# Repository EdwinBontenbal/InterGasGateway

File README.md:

# InterGasGateway
Arduino (esp8266) Hardware/Software to monitor a Intergas boiler over rs232 interface (x5) of the intergas boiler to Domotica Software with the use of MQTT.

# What to expect
This project consists of:
-  Hardware -> Cable diagram of between the IntergasGateway and the boiler
-  Hardware -> IntergasGateway Schemetic based on KiKad
-  Hardware -> IntergasGateway PCB based on KiKad
-  Software -> IntergasGateway sketch to be placed on arduino eps8266

# Hardware
A few requirements, set by myself, according to the hardware:
- Should be able to run paricitair on the boiler x5 PCB connector (without external power)
- High input RX/TX impedance
- RX/TX gavanically separated
- PCB should fitted in housing
- All parts can be ordered at Aliexpress
- PCb Easy to be ordered 
- Easy to build

# Software
A few requirements, set by myself, according to the software:
- Code should easy to read and logically setup
- Code should be expandable with ic3 burner
- Code should be based on statemachines
- Good serial debugging possibilities
- Output of retrieved data should be pushed to the serial port
- Output of retrieved data should be pushed to a mqtt listner (domotica software independent)
- Scheduled retrievel of data should be possible
- Reading the serial port should be fail save

# Usefull information
- When using the serial monitor function please set the speed to 115200
- The Gl_ParameterList als has a parameter to debug the serial port (ras data)

# Used tools
- Visual Studio code + platrformIO
- KiCad
- MQTT Explorer
- Python decompiler
- yed

# General requirements
- Based on opensource
- Robust
- Well documented
- Low cost
- Components easy to find and easy to order
- Reproducable

# Good to know
- Intergas has it's own software (IDS) for monitoring the X5 port of the boiler. You can download the original software at this link (https://www.intergas-verwarming.nl/zakelijk/download-ids-software/). The only thing you have to do is registrer yourself. The software was extremly usefull during the development of the arduino software.

# Help needed
I own a intergas boiler of type ic2 so I was able to develop the arduino parse code for the ic2 telegrams. I want to add and test also the ic3 telegrams therefor I need someone to test for me the arduino code. 

# Link to get the board

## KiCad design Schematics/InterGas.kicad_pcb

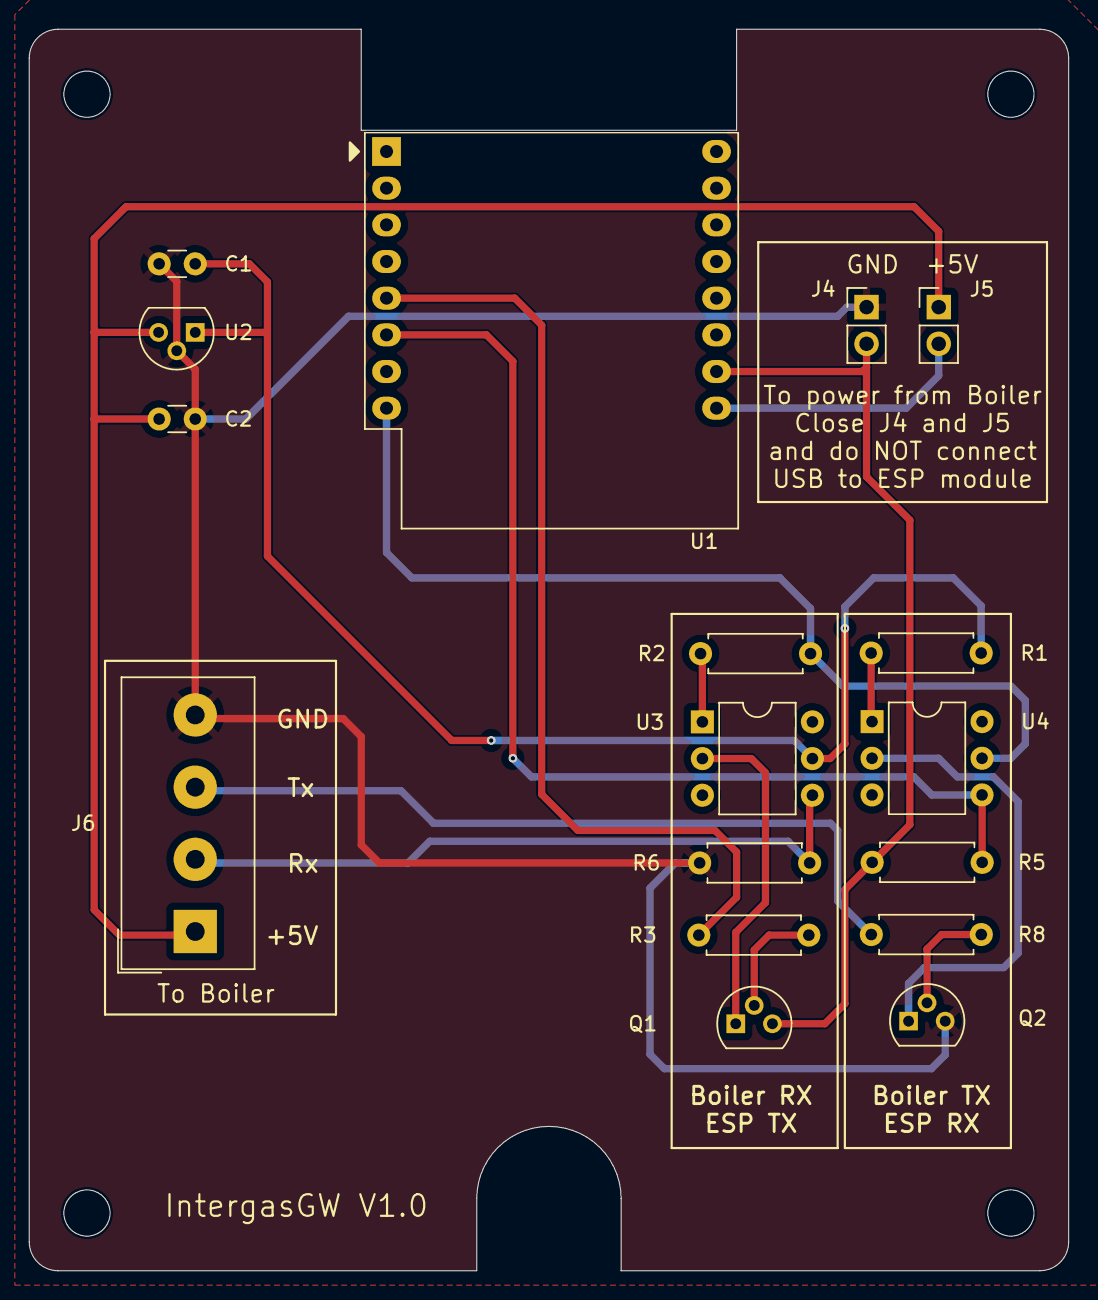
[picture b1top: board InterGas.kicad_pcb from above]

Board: 2 copper layers, 72.0 x 86.0 mm, 21 parts (0 on the bottom side), 16 nets.

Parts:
C1: 10nF; C_Disc_D3.0mm_W1.6mm_P2.50mm
C2: 100nF; C_Disc_D3.0mm_W1.6mm_P2.50mm
H1, H2, H3, H4: MountingHole; MountingHole_3.2mm_M3
J4, J5: Conn_01x02_Pin; PinHeader_1x02_P2.54mm_Vertical
J6: Screw_Terminal_01x04; Altech_AK100_1x04_P5.00mm
Q1, Q2: BC337; TO-92L
R1, R2, R3, R5, R6, R8: 1K; R_Axial_DIN0207_L6.3mm_D2.5mm_P7.62mm_Horizontal
U1: WEMOS_D1_mini; WEMOS_D1_mini_light
U2: L78L33_TO92; TO-92L
U3, U4: 4N25; DIP-6_W7.62mm

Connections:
+3V3 ESP8266: R2.2, U1.8 (3V3), U4.5
+3V3 Intergas: C1.1, R1.2, U2.1 (VO), U3.5
+5V ESP8266: J5.2, U1.9 (5V)
+5V Intergas: C2.1, J5.1, J6.1, U2.3 (VI)
Boiler_Rx: J6.2, R6.2, U3.4
Boiler_Tx: J6.3, R8.1
ESP32_Rx: R5.2, U1.6 (MOSI/D7), U4.4
ESP32_Tx: R3.1, U1.5 (MISO/D6)
GND ESP8266: J4.2, Q1.3 (E), R5.1, U1.10 (GND)
GND Intergas: C1.2, C2.2, J4.1, J6.4, Q2.3 (E), R6.1, U2.2 (GND)
unnamed: Q1.2 (B), R3.2
unnamed: Q1.1 (C), U3.2
unnamed: Q2.2 (B), R8.2
unnamed: Q2.1 (C), U4.2
unnamed: R1.1, U4.1
unnamed: R2.1, U3.1

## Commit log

2025-02-03 UpdatePictures
    1st picture update
2025-02-03 1st start schematics
2025-02-04 update
    update
2025-02-05 Update
    Update information found
2025-02-12 Create CasingDimensions.PNG
    Added dimensions of the casing for PCB
2025-02-12 Create DrillHoles_PCB.png
    Drill holes for PCB
2025-03-02 Test Setup
2025-04-06 OpenHab Files
    Openhab files for importing channel config
2025-04-06 Update README.md
    First step for documenting the project
2025-04-15 Update IntergasGateway__V0_9.ino
    Added reconnect function
    Added millis() rolover function
    Added duration of telegram
2025-04-16 Update README.md
    Added Hardware/Software requirements
2025-07-06 Lots of updates including statemachine
2025-08-15 Update Schematics
2025-08-15 Update with last code
    Update with last code
2025-08-15 Update readme
    Update readme
2025-08-15 Build Pictures Added
2025-08-15 Update
    - Statemachine
    - README
2025-08-15 Added Schematics
    - cable
    - board
2025-08-17 MQTT Examples added
2025-08-28 some modifications
    * Added mqtt user and password
    * enable option added per telegram
    * Improved emptyserialbuffer function
2025-08-28 Added burner id
    Added burner id in serial stream at startup
